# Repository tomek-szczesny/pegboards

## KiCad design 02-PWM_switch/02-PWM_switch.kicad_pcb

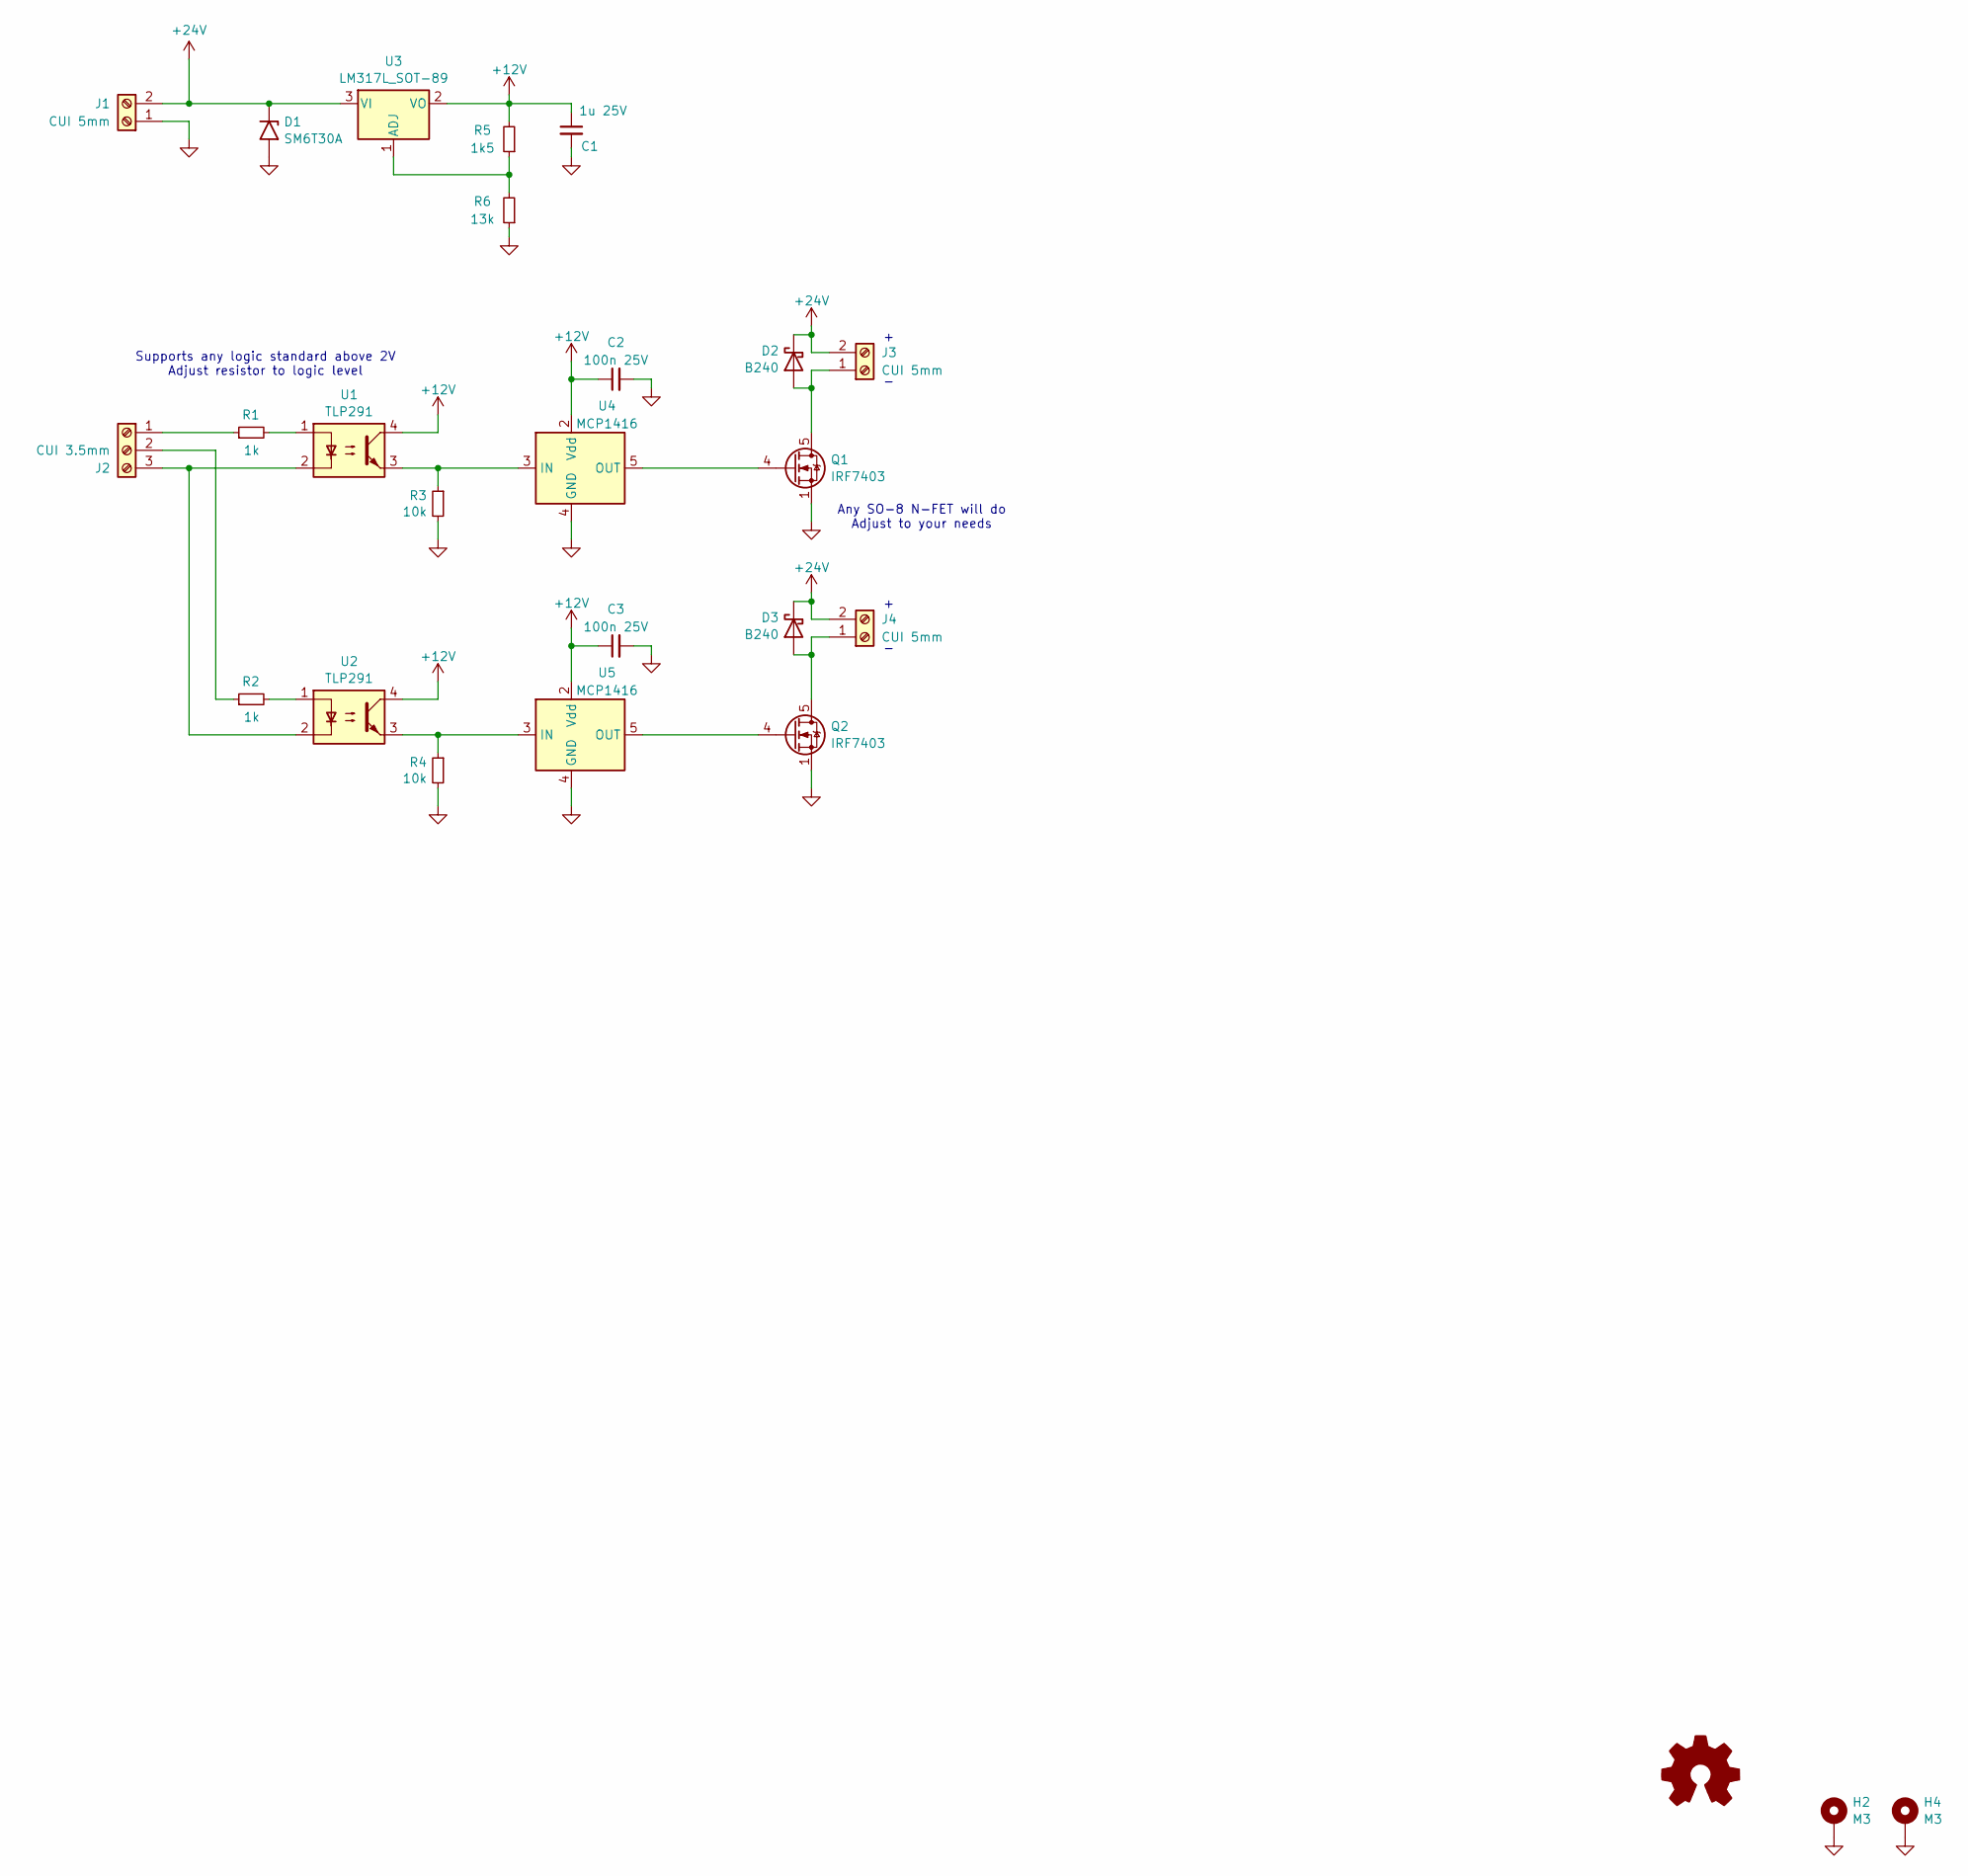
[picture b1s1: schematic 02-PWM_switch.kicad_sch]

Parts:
C1: 1u 25V; C_0603_1608Metric; LCSC C15849
C2, C3: 100n 25V; C_0603_1608Metric; LCSC C14663
D1: SM6T30A; D_SMB; LCSC C110904
D2, D3: B240; D_SMB; LCSC C110483
H2, H4: M3; MountingHole_3.2mm_M3_DIN965_Pad
J1, J3, J4: CUI 5mm; CUI_TBP04R12-500-02BE
J2: CUI 3.5mm; CUI_TBP03R1-350-03BE
Q1, Q2: IRF7403; SOIC-8_3.9x4.9mm_P1.27mm; LCSC C334232
R1, R2: 1k; R_0603_1608Metric; LCSC C21190
R3, R4: 10k; R_0603_1608Metric; LCSC C25804
R5: 1k5; R_0603_1608Metric; LCSC C22843
R6: 13k; R_0603_1608Metric; LCSC C22797
SYM1: Logo_Open_Hardware_Small; OSHW-Logo_7.5x8mm_SilkScreen
U1, U2: TLP291; SOIC-4_4.55x2.6mm_P1.27mm; LCSC C55144
U3: LM317L_SOT-89; SOT-89-3; LCSC C112537
U4, U5: MCP1416; SOT-23-5; LCSC C83775

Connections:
+12V: C1.1, C2.1, C3.1, R5.2, U1.4, U2.4, U3.2 (VO), U4.2 (Vdd), U5.2 (Vdd)
+24V: D1.1 (A1), D2.1 (K), D3.1 (K), J1.2, J3.2, J4.2, U3.3 (VI)
GND: C1.2, C2.2, C3.2, D1.2 (A2), H2.1, H4.1, J1.1, Q1.1 (S), Q1.2 (S), Q1.3 (S), Q2.1 (S), Q2.2 (S), Q2.3 (S), R3.2, R4.2, R6.1, U4.4 (GND), U5.4 (GND)
unnamed: D2.2 (A), J3.1, Q1.5 (D), Q1.6 (D), Q1.7 (D), Q1.8 (D)
unnamed: D3.2 (A), J4.1, Q2.5 (D), Q2.6 (D), Q2.7 (D), Q2.8 (D)
unnamed: J2.1, R1.1
unnamed: J2.2, R2.1
unnamed: J2.3, U1.2, U2.2
unnamed: Q1.4 (G), U4.5 (OUT)
unnamed: Q2.4 (G), U5.5 (OUT)
unnamed: R1.2, U1.1
unnamed: R2.2, U2.1
unnamed: R5.1, R6.2, U3.1 (ADJ)
unnamed: R3.1, U1.3, U4.3 (IN)
unnamed: R4.1, U2.3, U5.3 (IN)

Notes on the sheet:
Any SO-8 N-FET will do Adjust to your needs
Supports any logic standard above 2V Adjust resistor to logic level

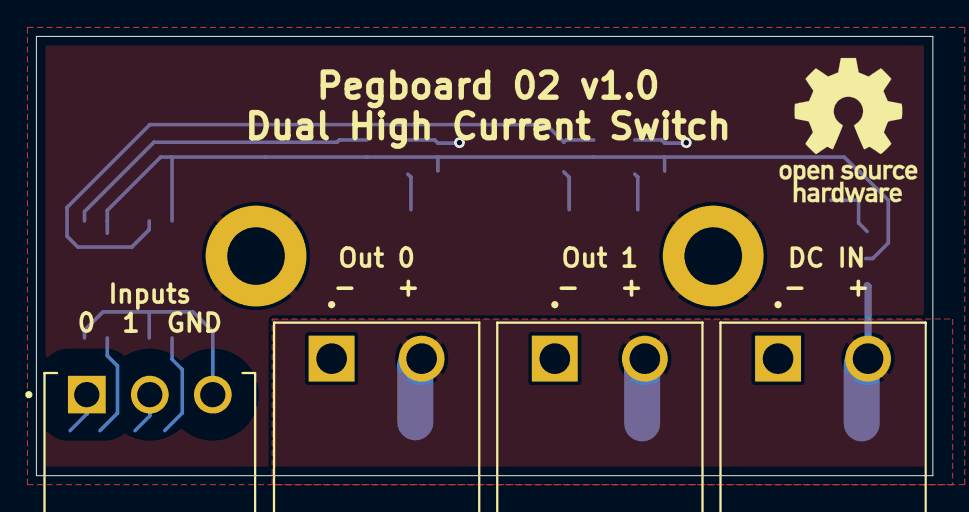
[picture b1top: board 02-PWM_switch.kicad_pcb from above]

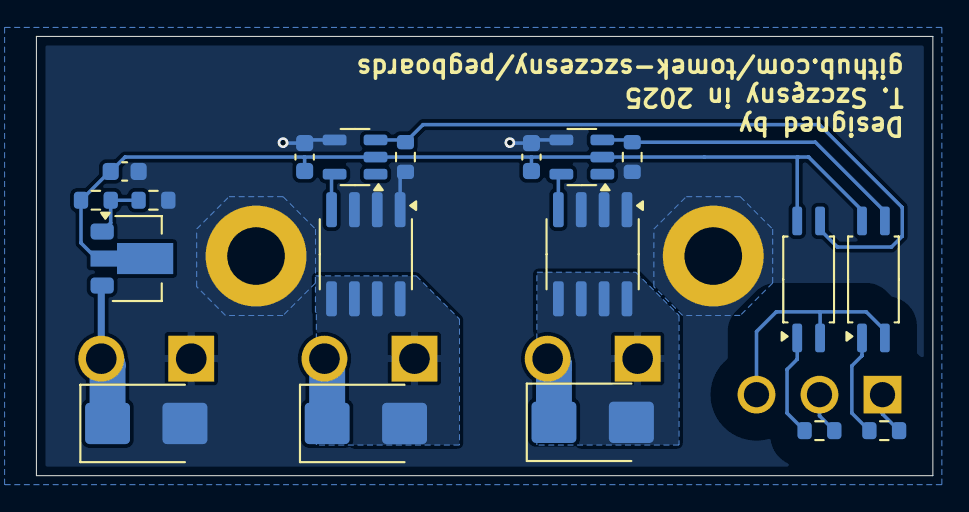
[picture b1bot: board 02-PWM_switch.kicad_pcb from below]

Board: 2 copper layers, 49.8 x 24.4 mm, 26 parts (19 on the bottom side), 15 nets.

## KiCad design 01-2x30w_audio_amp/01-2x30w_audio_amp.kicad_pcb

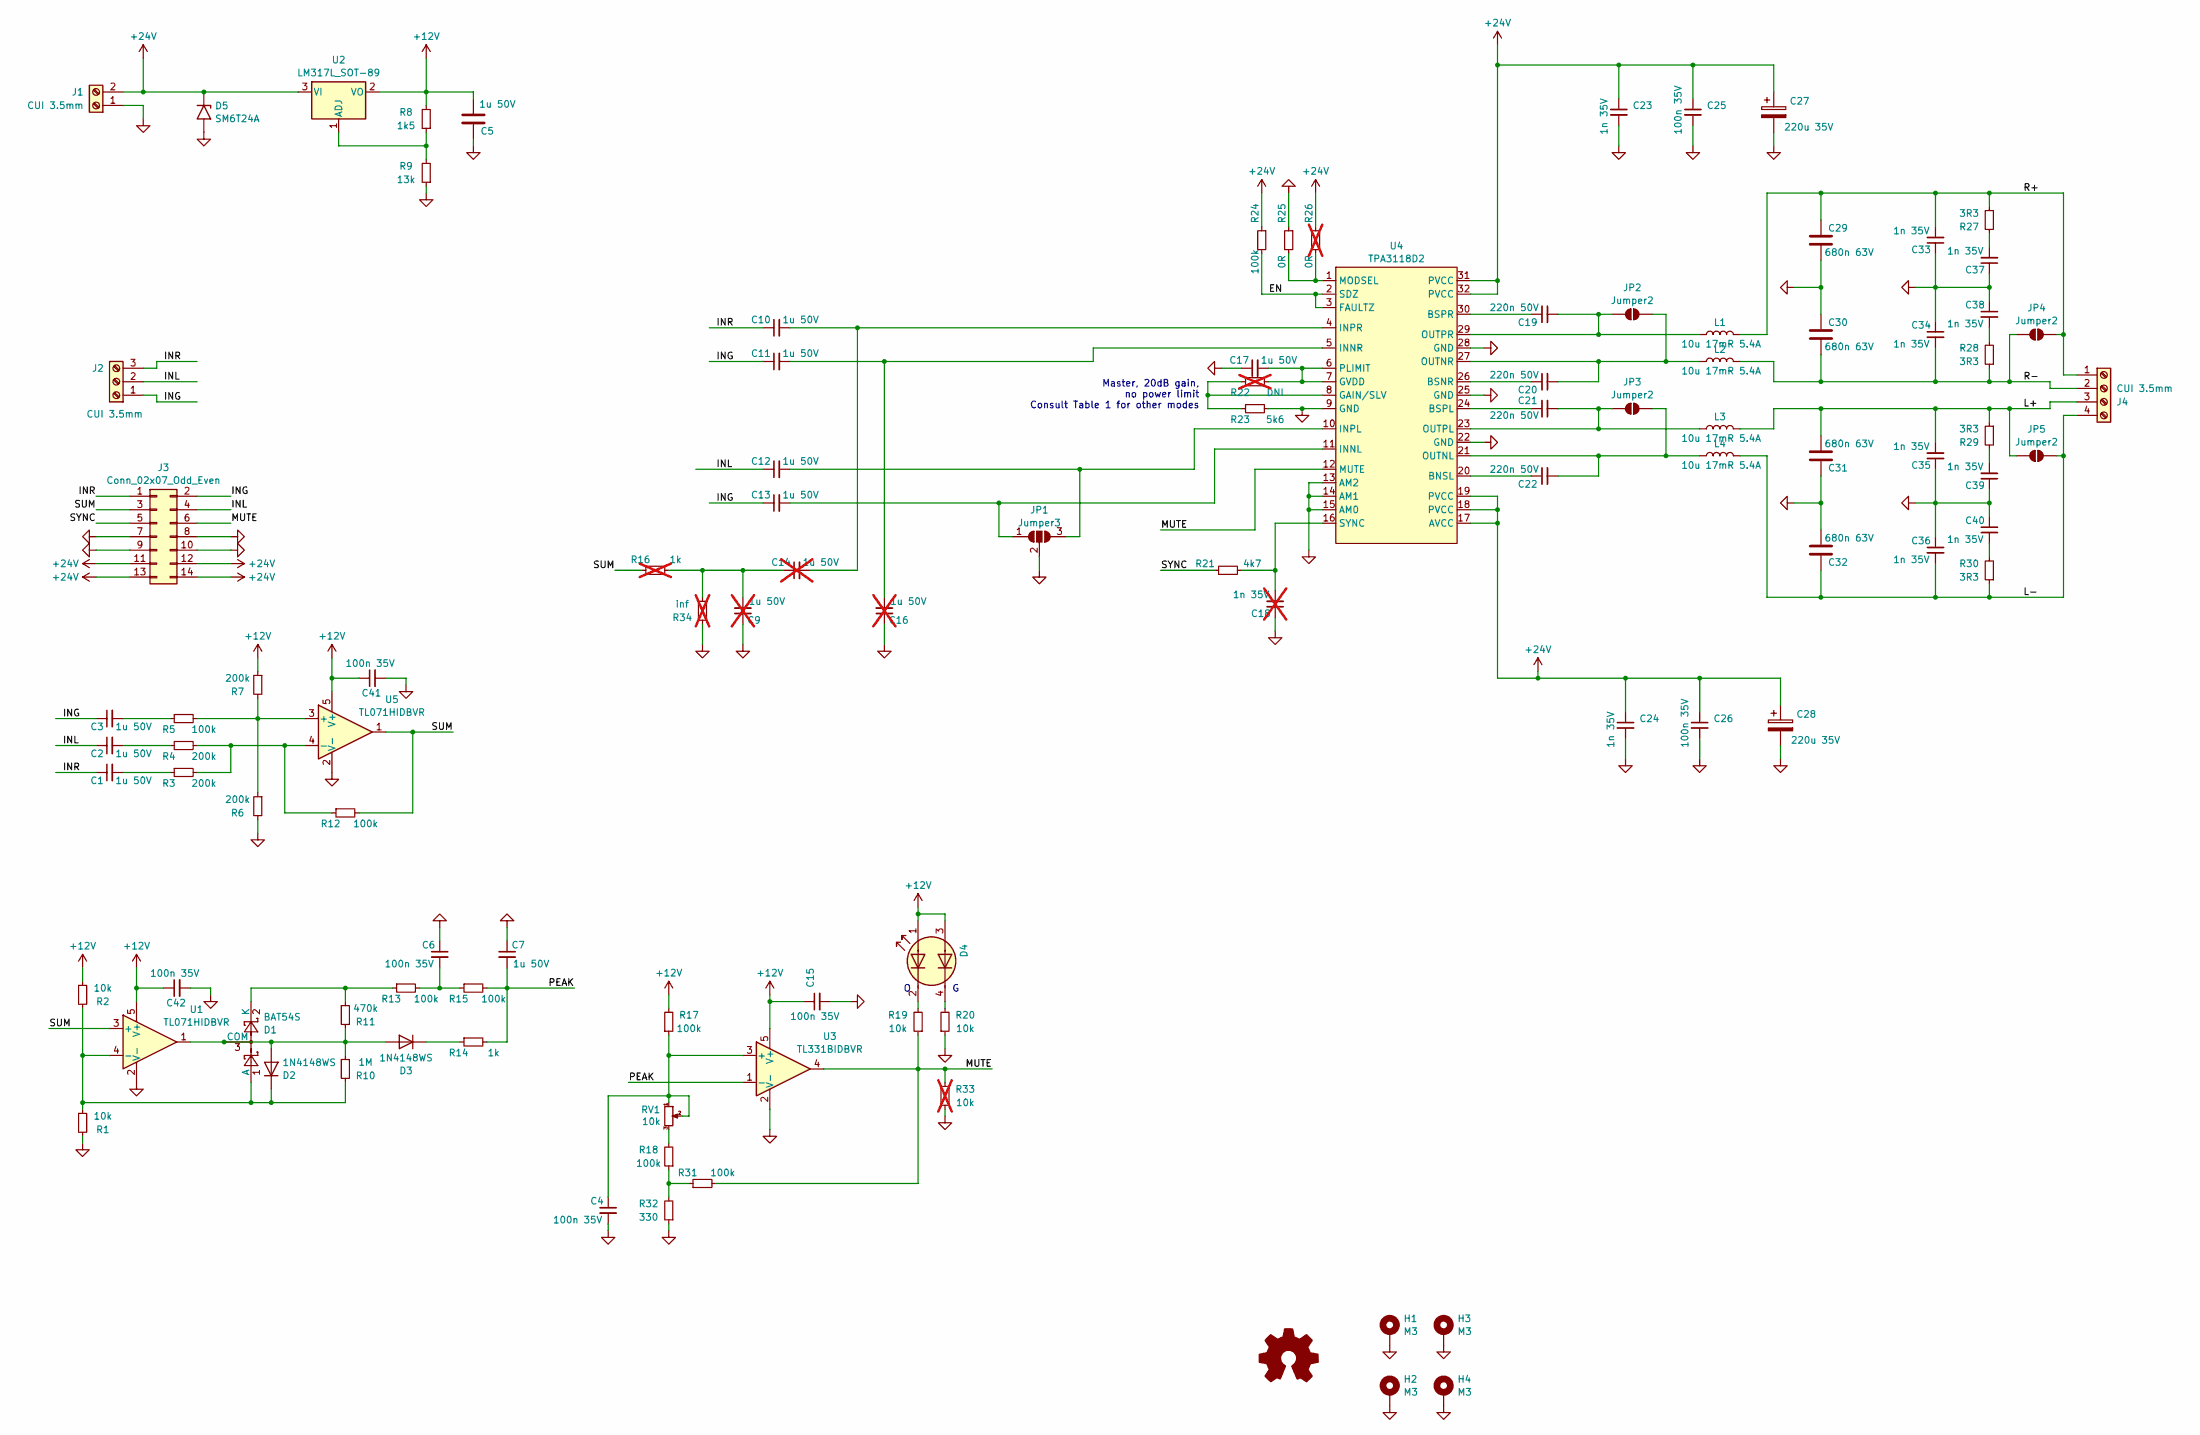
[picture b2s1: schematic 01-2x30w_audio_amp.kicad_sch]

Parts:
C1, C2, C3, C5, C7, C10, C11, C12, C13, C17: 1u 50V; C_0603_1608Metric; LCSC C15849
C4, C6, C15, C25, C26, C41, C42: 100n 35V; C_0603_1608Metric; LCSC C14663
C9, C14, C16: 1u 50V; C_0603_1608Metric; LCSC C15849; not fitted
C18: 1n 35V; C_0603_1608Metric; LCSC C1588; not fitted
C19, C20, C21, C22: 220n 50V; C_0603_1608Metric; LCSC C64705
C23, C24, C33, C34, C35, C36, C37, C38, C39, C40: 1n 35V; C_0603_1608Metric; LCSC C1588
C27, C28: EEUFR1V221; CP_Radial_D8.0mm_P3.50mm
C29, C30, C31, C32: B32529C684J; C_Rect_L7.2mm_W2.5mm_P5.00mm_FKS2_FKP2_MKS2_MKP2
D1: BAT54S; SOT-23; LCSC C47546
D2, D3: 1N4148WS; D_SOD-323; LCSC C2128
D4: MHK2396YGBTD; LED-TH_MHK2396YGBTD; LCSC C2764899
D5: SM6T24A; D_SMB; LCSC C3706522
H1, H2, H3, H4: M3; MountingHole_3.2mm_M3_DIN965_Pad
J1: CUI 3.5mm; CUI_TBP03R1-350-02BE; LCSC C3581450
J2: CUI 3.5mm; CUI_TBP03R1-350-03BE; LCSC C41784201
J3: Conn_02x07_Odd_Even; PinHeader_2x07_P2.54mm_Vertical
J4: CUI 3.5mm; CUI_TBP03R1-350-04BE
JP1: Jumper3; SolderJumper-3_P1.3mm_Open_RoundedPad1.0x1.5mm
JP2, JP3, JP4, JP5: Jumper2; SolderJumper-2_P1.3mm_Open_RoundedPad1.0x1.5mm
L1, L2, L3, L4: RFS1113-103ME; L_Radial_D10.5mm_P5.00mm_Abacron_AISR-01
R1, R2, R19, R20: 10k; R_0603_1608Metric; LCSC C25804
R3, R4, R6, R7: 200k; R_0603_1608Metric; LCSC C25811
R5, R12, R13, R15, R17, R18, R24, R31: 100k; R_0603_1608Metric; LCSC C25803
R8: 1k5; R_0603_1608Metric; LCSC C22843
R9: 13k; R_0603_1608Metric; LCSC C22797
R10: 1M; R_0603_1608Metric; LCSC C22935
R11: 470k; R_0603_1608Metric; LCSC C23178
R14: 1k; R_0603_1608Metric; LCSC C21190
R16: 1k; R_0603_1608Metric; LCSC C21190; not fitted
R21: 4k7; R_0603_1608Metric; LCSC C23162
R22: DNI; R_0603_1608Metric; not fitted
R23: 5k6; R_0603_1608Metric; LCSC C23189
R25: 0R; R_0603_1608Metric; LCSC C21189
R26: 0R; R_0603_1608Metric; LCSC C21189; not fitted
R27, R28, R29, R30: 3R3; R_0603_1608Metric; LCSC C22939
R32: 330; R_0603_1608Metric; LCSC C23138
R33: 10k; R_0603_1608Metric; LCSC C25804; not fitted
R34: inf; R_0603_1608Metric; LCSC C25804; not fitted
RV1: PT6KH-103A2020; Potentiometer_Piher_PT-6-H_Horizontal
SYM1: Logo_Open_Hardware_Small; OSHW-Logo_7.5x8mm_SilkScreen
U1, U5: TL071HIDBVR; SOT-23-5; LCSC C4370629
U2: LM317L_SOT-89; SOT-89-3; LCSC C112537
U3: TL331BIDBVR; SOT-23-5; LCSC C2877827
U4: TPA3118D2; HTSSOP-32-1EP_6.1x11mm_P0.65mm_EP5.2x11mm_Mask4.11x4.36mm_T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; LCSC C46497

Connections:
+12V: C5.1, C15.1, C41.1, C42.1, D4.1 (K1), D4.3 (K2), R2.1, R7.1, R8.2, R17.2, U1.5 (V+), U2.2 (VO), U3.5 (V+), U5.5 (V+)
+24V: C23.1, C24.1, C25.1, C26.1, C27.1, C28.1, D5.1 (A1), J1.2, J3.11, J3.12, J3.13, J3.14, R24.1, R26.1, U2.3 (VI), U4.17 (AVCC), U4.18 (PVCC), U4.19 (PVCC), U4.31 (PVCC), U4.32 (PVCC)
/EN: R24.2, U4.2 (SDZ), U4.3 (FAULTZ)
/ING: C3.1, C11.1, C13.1, J2.1, J3.2
/INL: C2.1, C12.1, J2.2, J3.4
/INR: C1.1, C10.1, J2.3, J3.1
/L+: C31.1, C35.2, J4.3, JP5.2 (B), L3.2, R29.1
/L-: C32.2, C36.2, J4.4, JP5.1 (A), L4.2, R30.1
/MUTE: J3.6, R19.1, R31.2, R33.2, U3.4, U4.12 (MUTE)
/PEAK: C7.2, R14.2, R15.2, U3.1 (-)
/R+: C29.2, C33.2, J4.1, JP4.1 (A), L1.2, R27.1
/R-: C30.1, C34.2, J4.2, JP4.2 (B), L2.2, R28.1
/SUM: J3.3, R12.2, R16.1, U1.3 (+), U5.1
/SYNC: J3.5, R21.1
GND: C4.2, C5.2, C6.1, C7.1, C9.1, C15.2, C16.1, C17.1, C18.1, C23.2, C24.2, C25.2, C26.2, C27.2, C28.2, C29.1, C30.2, C31.2, C32.1, C33.1, C34.1, C35.1, C36.1, C37.1, C38.1, C39.1, C40.1, C41.2, C42.2, D5.2 (A2), H1.1, H2.1, H3.1, H4.1, J1.1, J3.7, J3.8, J3.9, J3.10, JP1.2 (C), R1.2, R6.2, R9.1, R20.1, R23.2, R25.1, R32.1, R33.1, R34.2, U1.2 (V-), U3.2 (V-), U4.9 (GND), U4.13 (AM2), U4.14 (AM1), U4.15 (AM0), U4.22 (GND), U4.25 (GND), U4.28 (GND), U4.33 (PAD), U5.2 (V-)
unnamed: C1.2, R3.1
unnamed: C2.2, R4.1
unnamed: C3.2, R5.1
unnamed: C6.2, R13.2, R15.1
unnamed: C9.2, C14.1, R16.2, R34.1
unnamed: C37.2, R27.2
unnamed: C38.2, R28.2
unnamed: C39.2, R29.2
unnamed: C40.2, R30.2
unnamed: D1.1 (A), D2.1 (K), R1.1, R2.2, R10.2, U1.4 (-)
unnamed: D1.3 (COM), D2.2 (A), D3.2 (A), R10.1, R11.2, U1.1
unnamed: D1.2 (K), R11.1, R13.1
unnamed: D3.1 (K), R14.1
unnamed: D4.2 (A1), R19.2
unnamed: D4.4 (A2), R20.2
unnamed: C13.2, JP1.1 (A), U4.11 (INNL)
unnamed: C12.2, JP1.3 (B), U4.10 (INPL)
unnamed: C20.2, JP2.1 (A), L2.1, U4.27 (OUTNR)
unnamed: C19.2, JP2.2 (B), L1.1, U4.29 (OUTPR)
unnamed: C22.2, JP3.1 (A), L4.1, U4.21 (OUTNL)
unnamed: C21.2, JP3.2 (B), L3.1, U4.23 (OUTPL)
unnamed: R18.1, R31.1, R32.2
unnamed: R18.2, RV1.3
unnamed: R8.1, R9.2, U2.1 (ADJ)
unnamed: C4.1, R17.1, RV1.1, RV1.2, U3.3 (+)
unnamed: C22.1, U4.20 (BNSL)
unnamed: C20.1, U4.26 (BSNR)
unnamed: C21.1, U4.24 (BSPL)
unnamed: C19.1, U4.30 (BSPR)
unnamed: R22.1, R23.1, U4.8 (GAIN/SLV)
unnamed: C17.2, R22.2, U4.6 (PLIMIT), U4.7 (GVDD)
unnamed: C11.2, C16.2, U4.5 (INNR)
unnamed: C10.2, C14.2, U4.4 (INPR)
unnamed: R25.2, R26.2, U4.1 (MODSEL)
unnamed: C18.2, R21.2, U4.16 (SYNC)
unnamed: R5.2, R6.1, R7.2, U5.3 (+)
unnamed: R3.2, R4.2, R12.1, U5.4 (-)

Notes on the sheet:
Master, 20dB gain, no power limit Consult Table 1 for other modes

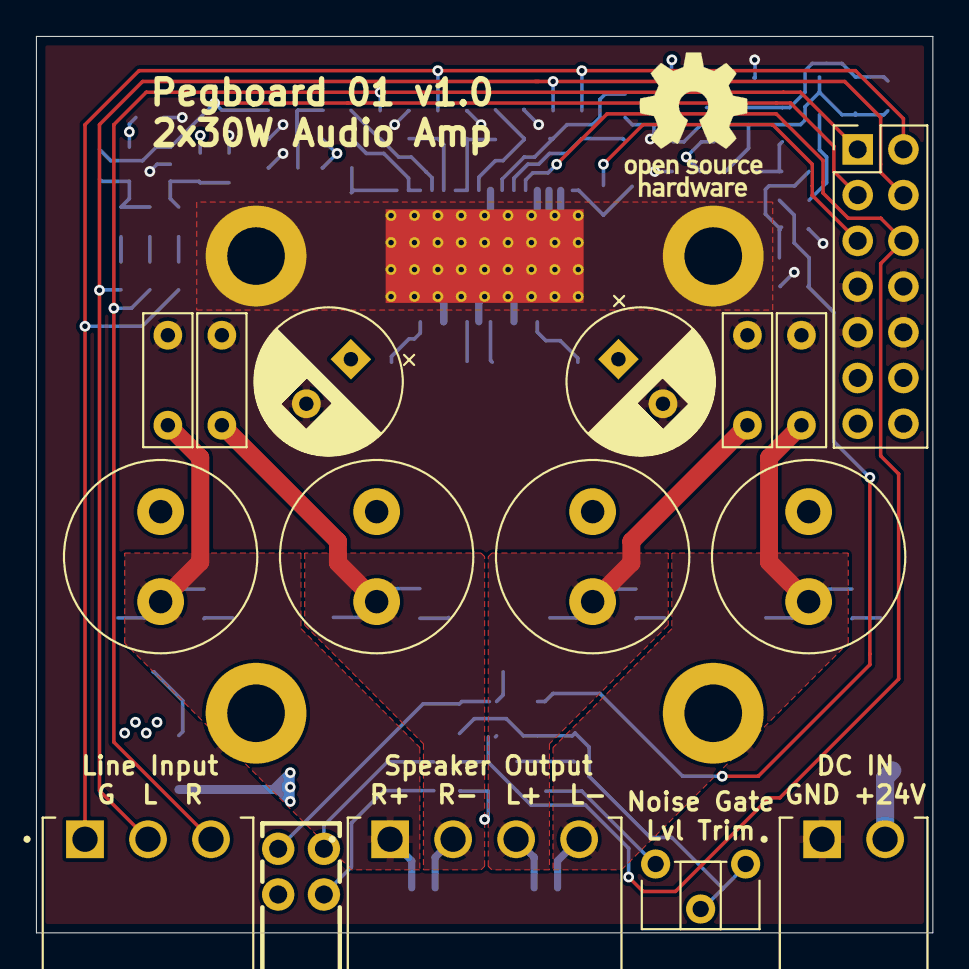
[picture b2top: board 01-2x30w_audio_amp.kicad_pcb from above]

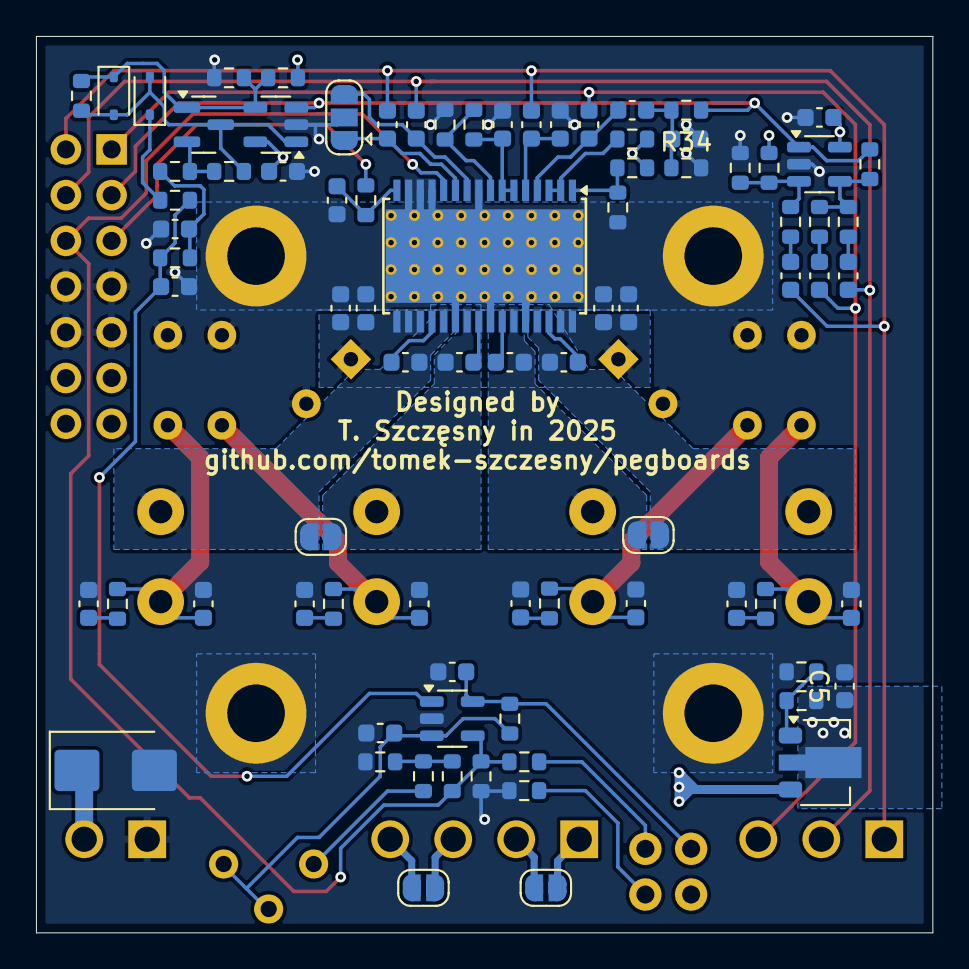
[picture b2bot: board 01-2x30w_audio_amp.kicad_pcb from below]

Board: 4 copper layers, 49.8 x 49.8 mm, 104 parts (83 on the bottom side), 52 nets.

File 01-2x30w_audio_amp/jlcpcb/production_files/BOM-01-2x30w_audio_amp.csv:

Comment,Designator,Footprint,LCSC,Quantity
LM317L_SOT-89,U2,SOT-89-3,C112537,1
100n 35V,"C15,C25,C26,C4,C41,C42,C6",C_0603_1608Metric,C14663,7
1u 50V,"C1,C10,C11,C12,C13,C17,C2,C3,C5,C7",C_0603_1608Metric,C15849,10
1n 35V,"C23,C24,C33,C34,C35,C36,C37,C38,C39,C40",C_0603_1608Metric,C1588,10
0R,R25,R_0603_1608Metric,C21189,1
1k,R14,R_0603_1608Metric,C21190,1
1N4148WS,"D2,D3",D_SOD-323,C2128,2
13k,R9,R_0603_1608Metric,C22797,1
1k5,R8,R_0603_1608Metric,C22843,1
1M,R10,R_0603_1608Metric,C22935,1
3R3,"R27,R28,R29,R30",R_0603_1608Metric,C22939,4
330,R32,R_0603_1608Metric,C23138,1
4k7,R21,R_0603_1608Metric,C23162,1
470k,R11,R_0603_1608Metric,C23178,1
5k6,R23,R_0603_1608Metric,C23189,1
100k,"R12,R13,R15,R17,R18,R24,R31,R5",R_0603_1608Metric,C25803,8
10k,"R1,R19,R2,R20",R_0603_1608Metric,C25804,4
200k,"R3,R4,R6,R7",R_0603_1608Metric,C25811,4
MHK2396YGBTD,D4,LED-TH_MHK2396YGBTD,C2764899,1
TL331BIDBVR,U3,SOT-23-5,C2877827,1
SM6T24A,D5,D_SMB,C3706522,1
TL071HIDBVR,"U1,U5",SOT-23-5,C4370629,2
TPA3118D2,U4,HTSSOP-32-1EP_6.1x11mm_P0.65mm_EP5.2x11mm_Mask4.11x4.36mm_ThermalVias,C46497,1
BAT54S,D1,SOT-23,C47546,1
220n 50V,"C19,C20,C21,C22",C_0603_1608Metric,C64705,4
B32529C684J,C30,C_Rect_L7.2mm_W2.5mm_P5.00mm_FKS2_FKP2_MKS2_MKP2,,1
EEUFR1V221,C27,CP_Radial_D8.0mm_P3.50mm,,1
B32529C684J,C29,C_Rect_L7.2mm_W2.5mm_P5.00mm_FKS2_FKP2_MKS2_MKP2,,1
B32529C684J,C32,C_Rect_L7.2mm_W2.5mm_P5.00mm_FKS2_FKP2_MKS2_MKP2,,1
B32529C684J,C31,C_Rect_L7.2mm_W2.5mm_P5.00mm_FKS2_FKP2_MKS2_MKP2,,1
EEUFR1V221,C28,CP_Radial_D8.0mm_P3.50mm,,1

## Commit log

2025-03-08 The first commit of the first module
2025-03-09 Minor tweaks
2025-03-09 Pegboard number 02
2025-03-09 Moved module 02
2025-03-26 Base boards template
2025-03-30 Code cleanup and a new mount pattern
